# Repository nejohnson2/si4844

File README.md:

# SI4844 FM Radio

This is an FM radio using the digital reciever module ```Si4844```. 

- [Si4844 Demo](https://www.silabs.com/documents/public/user-guides/Si4844-B-DEMO.pdf)
- [All About Circuits](http://www.allaboutcircuits.com/projects/build-an-arduino-controlled-am-fm-sw-radio/) - this is the original blog post about setting up radio
- [Design Guide](http://www.silabs.com/Support%20Documents/TechnicalDocs/AN602.pdf)
- [Programming Guide](http://www.silabs.com/Support%20Documents/TechnicalDocs/AN610.pdf)

## STATUS

- [x] Circuit Power
- [x] I2C Communication
- [x] Si4844 power
- [x] FM demodulation
- [x] Basic functionality

To do:
- [ ] Add Band switch
- [ ] Add display
- [ ] On/Off switch
- [ ] Audio out (?)
- [ ] Move to protoboard
- [ ] Enhanced audio amplifier
- [ ] Enhanced AM/FM antenna
- [ ] Buy knobs/dials
- [ ] [Enclosure](https://s-media-cache-ak0.pinimg.com/originals/ba/01/3a/ba013af739433c9e4d94a3727d0fa14c.jpg)

## Build Notes

## Microcontroller 
 ~~The original blog post uses an Arduino 3.3v Pro Mini.  I dont have one of these so instead I'm using a Teensy 3.2.  The main reason I'm going with the Teensy is that it's also a 3.3v board.  I've also thought about using a ```3.3v Trinket Pro``` but I dont have my 3.3v-5v serial adapter.  The ```Teensy 3.2``` has built in serial converter.~~ 

I've decided to get really complicated and use an **ATMEGA328P** chip.  [This page](https://www.arduino.cc/en/Main/Standalone) describes the process of setting up a standalone ATMEGA328P.

## Power
It is suggested to power the whole board from a 3.3v regulator and not the microcontroller as the microcontroller will not supply enough amps.

## Communication
The ```Si4844``` is an I2C slave device with an address ```0x11```.  The ```Si4844``` maximum speed is 50kHz and during some parts of the startup phase, the speed must not exceed 10kHz.  With Arduino, you can use the ```Wire``` library and change the I2C speed with ```Wire.setClock(10000)``` which sets the I2C clock speed to 10k.  I used 2.2k pullup resistors for both the SDA and SCK lines.

## Audio
~~I'm using a basic audio amplifyer circut using the LM386.  The schematic from the datasheet is: ~~

~~I also used [this website](http://www.circuitbasics.com/build-a-great-sounding-audio-amplifier-with-bass-boost-from-the-lm386/) to enhance the circuit. ~~

The working audio schematic is located [here](https://www.instructables.com/id/Tales-From-the-Chip-LM386-Audio-Amplifier/).

## Antenna
The setup works without any 'official' antenna.  I basically have a 6 inch wire twisted once which is providing quality reception.

## Parts

- [ ] [Si4844-B20](http://www.digikey.com/product-detail/en/silicon-labs/SI4844-B20-GU/SI4844-B20-GU-ND/4069445) - Receiver
- [ ] [TPA3123](http://www.digikey.com/product-detail/en/texas-instruments/TPA3123D2PWPR/296-22008-1-ND/1649103) - Class D Audio Amp

## Final Design

- [ ] On/Off toggle
- [ ] Excellent stereo audio quality
- [ ] Volume knob
- [ ] FM Tuning Knob
- [ ] External antenna option

## Misc Parts

Radio dial inspiration comes from a [1934-36 Zenith 5-S-29](https://s-media-cache-ak0.pinimg.com/564x/3f/08/86/3f08869ec74c9f22957f4a435a4101e7.jpg).  [Here](http://www.radioblvd.com/ZenithPhoto.htm) is a list of all Zenith models.

- [ ] Escutcheone
- [ ] Zenith 6-2-229 Chasis
- [ ] Knobs

### Useful Links

- [Dial Cord String Guide](http://www.theoldradiofixerupperguy.com/dial%20cord.html)
- [Old Radio Zone](http://www.oldradiozone.com/zenith.html)
- [Phil's Old Radios](https://www.antiqueradio.org/wooden.htm)

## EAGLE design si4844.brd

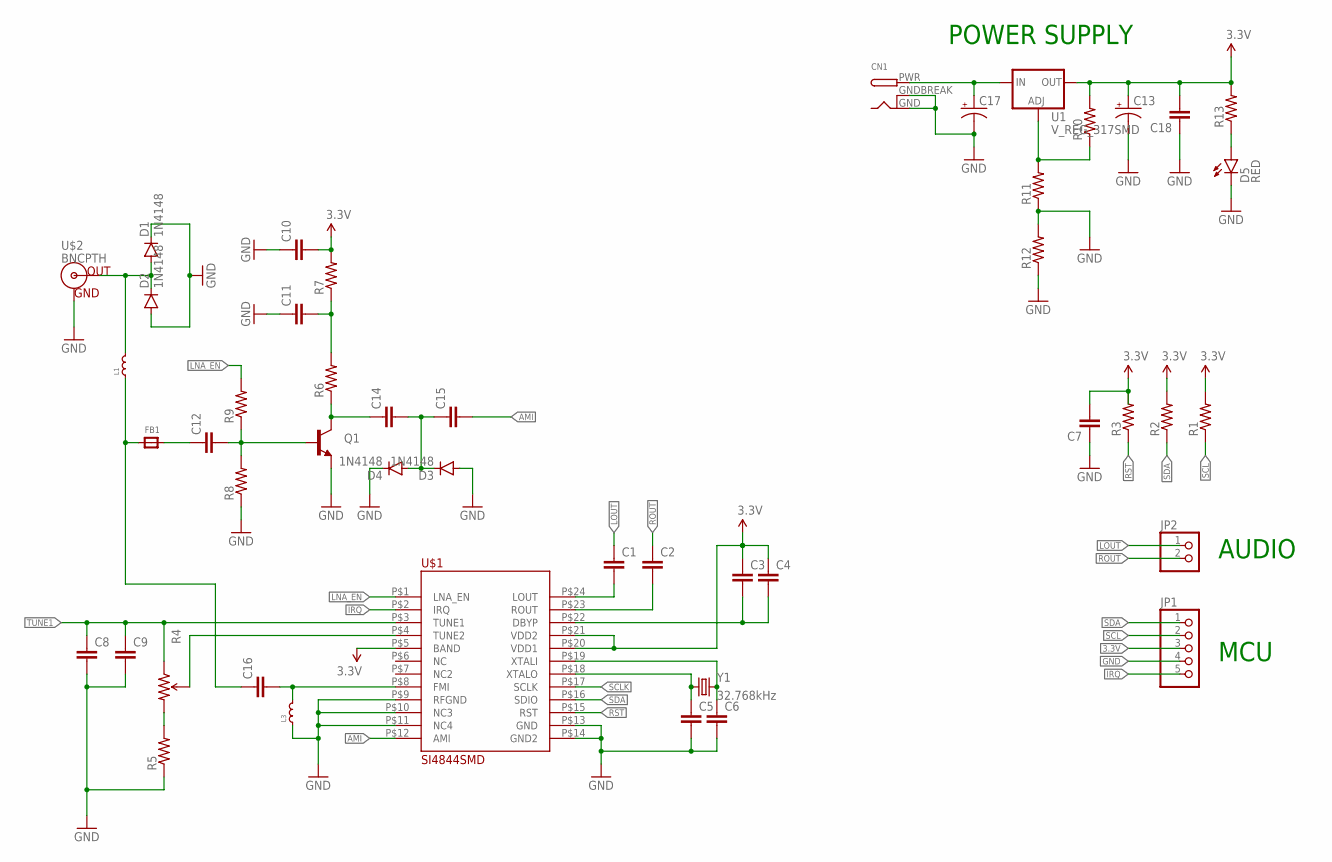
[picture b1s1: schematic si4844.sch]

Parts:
C1, C2, C3, C4, C5, C6, C7, C8, C9, C10, C11, C12, C14, C15, C16, C18: CAP0603-CAP; 0603-CAP
C13, C17: CAP_POL1206-KIT; EIA3216-KIT
CN1: DCBARRELPTH; DCJACK_2MM_PTH
D1, D2, D3, D4: 1N4148; DIODE-1N4148
D5: RED; LED-1206
FB1: FERRITE_0603; _0603
JP1: HEADER-1X5; 1X05_OVAL
JP2: HEADER-1X2; 1X02_OVAL
L1, L3: RF-INDUCTOR.0603; 0603
Q1: TRANSISTOR_NPNBC547; TO-92-AMMO
R1, R2, R3, R5, R6, R7, R8, R9, R10, R11, R12, R13: RESISTOR0603-RES; 0603-RES
R4: TRIMPOT3362U-2; 3362U-2
U1: V_REG_317SMD; SOT223
U$1: SI4844SMD; SSOP24
U$2: BNCPTH; BNC
Y1: 32.768kHz; CRYSTAL-SMD-3.2X1.5MM

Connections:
3.3V: C3.1, C4.1, C7.2, C10.2, C13.A (+), C18.2, JP1.3, R1.2, R2.2, R3.2, R7.2, R10.2, R13.2, U1.2 (OUT), U$1.P$5 (BAND), U$1.P$20 (VDD1), U$1.P$21 (VDD2)
AMI: C15.2, U$1.P$12 (AMI)
FMI: C16.1, FB1.1, L1.1
GND: C5.2, C6.2, C7.1, C8.2, C9.2, C10.1, C11.1, C13.C (-), C17.C (-), C18.1, CN1.GND, CN1.GNDBREAK, D1.C, D2.A, D3.A, D4.C, D5.C, JP1.4, L3.1, Q1.3 (E), R5.1, R8.1, R11.1, R12.1, R12.2, U$1.P$9 (RFGND), U$1.P$10 (NC3), U$1.P$11 (NC4), U$1.P$13 (GND), U$1.P$14 (GND2), U$2.GND
IRQ: JP1.5, U$1.P$2 (IRQ)
LNA_EN: R9.2, U$1.P$1 (LNA_EN)
LOUT: C1.1, JP2.1
unnamed: C1.2, U$1.P$24 (LOUT)
unnamed: C2.2, U$1.P$23 (ROUT)
unnamed: C3.2, C4.2, U$1.P$22 (DBYP)
unnamed: C5.1, U$1.P$18 (XTALO), Y1.P$1 (1)
unnamed: C11.2, R6.2, R7.1
unnamed: R4.2 (WIPER), U$1.P$4 (TUNE2)
unnamed: C12.2, Q1.2 (B), R8.2, R9.1
unnamed: C6.1, U$1.P$19 (XTALI), Y1.P$2 (2)
unnamed: C14.1, Q1.1 (C), R6.1
unnamed: R4.3 (CW), R5.2
unnamed: C14.2, C15.1, D3.C, D4.A
unnamed: C12.1, FB1.2
unnamed: D1.A, D2.C, L1.2, U$2.S (OUT)
unnamed: C17.A (+), CN1.PWR, U1.3 (IN)
unnamed: C16.2, L3.2, U$1.P$8 (FMI)
unnamed: R10.1, R11.2, U1.1 (ADJ)
unnamed: D5.A, R13.1
ROUT: C2.1, JP2.2
RST: R3.1, U$1.P$15 (RST)
SCL: JP1.2, R1.1
SCLK: U$1.P$17 (SCLK)
SDA: JP1.1, R2.1, U$1.P$16 (SDIO)
TUNE1: C8.1, C9.1, R4.1 (CCW), U$1.P$3 (TUNE1)

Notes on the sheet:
POWER SUPPLY
MCU
AUDIO

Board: 2 copper layers, 47 parts (0 on the bottom side), 29 nets, no tracks yet.

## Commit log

2016-12-12 init commit
2018-02-21 added audio schematics
2019-01-28 updated notes on the audio schematic

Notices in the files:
parts and their libraries:
SparkFun-Capacitors: Licensing: Creative Commons ShareAlike 4.0 International - https://creativecommons.org/licenses/by-sa/4.0
microbuilder: This work is placed in the public domain, and may be freely used for commercial and non-commercial work with the following conditions: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
